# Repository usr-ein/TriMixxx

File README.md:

# TriMixxx

A custom DJ media player — a CDJ-style deck — built from scratch around a Raspberry Pi, designed to run [Mixxx](https://mixxx.org/) DJ software. It reuses an original Pioneer CDJ's buttons and jog wheel behind custom PCBs and a 3D-printed chassis for an authentic DJ feel, and reads Rekordbox-formatted USB sticks — no laptop required.

### The screen

The 1024×600 touchscreen runs a purpose-built Mixxx skin (`mixxx_config/TriMixxx_skin`). There is no mouse and no laptop: every control is either on the deck or under a thumb, so the UI is built around big targets and the browse encoder rather than around pointer precision.

| Playing | Browsing |
|---|---|
|  |  |
| Scrolling waveform with the beat grid, red downbeats anchored on the intro cue, and the whole-track overview underneath. Tempo and pitch sit bottom-right; the header carries artwork, title/artist, the phase meter, elapsed/remaining and the underrun counter. | Rekordbox USBs, the local collection and the Pro DJ Link players lead the menu — the three a deck actually reaches for. The left column sizes itself to its content and follows the selection, and neither pane has a scrollbar: the encoder scrolls them. |

An active loop, set from the deck's hardware loop-in/out buttons, drawn as an amber window over the waveform. Nothing sits below it — the transport, hotcues, loop sizing and tempo range are all physical controls, so the screen gives that space back to the waveform.

## What is this?

TriMixxx replaces the internals of a Pioneer CDJ with modern, open-source-friendly hardware while keeping the physical controls that DJs know and love. Plug in a Rekordbox-formatted USB stick, and you're ready to mix.

Where the CDJ's original main board did everything, TriMixxx today is a **small distributed system**: a Raspberry Pi runs a patched Mixxx behind a custom CDJ-style skin, an ESP32-S3 acts as the controller brain that reads every physical control and speaks MIDI, and a swarm of tiny satellite boards handle the buttons and the LED rings. They all talk over plain TTL UART.

It is a working deck, not a plan: the Pi boots straight into Mixxx, the USB stick automounts, the S3's controls drive it, and Mixxx's feedback drives the LEDs back. Alongside that, `prolinks-compat/` has reverse-engineered Pioneer's ProLink protocol far enough that a real CDJ-2000NXS browses and plays tracks served by this project.

## How we got here (a short history)

This project has been through several complete redesigns. It's worth keeping the lineage straight:

1. **One board to rule them all.** The first idea was a single monolithic PCB carrying *everything*: a Raspberry Pi CM5, a TI PCM5242 I²S DAC with RCA + headphone outputs, USB-C PD power (CH224K + SY8368AQQC buck), dual micro-HDMI, the USB stick ports, and an **ATmega32U4** presenting the CDJ's buttons/jog/fader to the Pi as a USB-MIDI device — all on one board. It was fully routed (`screenshots/CDJ-MainBoard-v1_fully_routed.png`, and the `*_2026-02-17.png` schematic captures) but never became the working unit; cramming compute, audio, power, and a controller onto one board made every revision expensive and every mistake fatal.

2. **Breaking it apart.** The controller was split out onto its own board. `boards/midi-laser-pcb` was the first standalone MIDI-controller PCB — it was fabricated, then abandoned in favour of a cleaner design.

3. **Where it is now.** `boards/midi_s3_mini` is the current controller board (fabricated), hosting a **LOLIN S3 Mini (ESP32-S3)**. The audio DAC and power delivery are no longer TriMixxx's job — a Raspberry Pi handles Mixxx and audio directly, and the S3 is purely the controller brain. The controls are spread across small purpose-built satellite boards, all of them already fabricated.

The old monolithic design is preserved in this README's history and in `screenshots/` as a record of the road not taken.

## Current architecture

```mermaid
flowchart LR
    subgraph PiBox["Raspberry Pi (deck)"]
        Mixxx["Mixxx (patched fork)<br/>+ TriMixxx skin"]
        Tty["ttymidi<br/>trimixxx-bridge.service"]
        Daemon["trimixxx-launchd<br/>(launch manager +<br/>SysEx to the OS)"]
        Usb["dj-usb automount<br/>/media/DJ_USB_*"]
        Doom["Doom (1993)<br/>hold PLAY at boot"]
        Keys["trimixxx-deckkeys<br/>MIDI -> /dev/uinput"]
    end

    S3["midi_s3_mini<br/>LOLIN S3 Mini / ESP32-S3<br/>(controller brain)"]
    RingA["OneButton ring A<br/>CH32V003 nodes<br/>button + 2xWS2812 each"]
    RingB["OneButton ring B<br/>CH32V003 nodes"]
    PlayCue["play_cue_btn<br/>Play / Cue + LEDs"]
    Loop["loop_btn<br/>Loop In/Out/Reloop + LEDs"]
    Jog["Jog wheel<br/>quadrature + touch"]
    CDJ["Real CDJs<br/>(ProLink, Ethernet)"]

    Mixxx <--> Tty
    Mixxx <-->|SysEx| Daemon
    Usb --> Daemon
    Daemon -->|"picks the boot mode"| Mixxx
    Daemon -->|"picks the boot mode"| Doom
    Daemon --> Keys
    Tty -->|"deck buttons"| Daemon
    Tty -->|"deck buttons"| Keys
    Keys -->|"virtual keyboard + mouse"| Doom
    Tty <-->|"UART - raw MIDI - 3.3V"| S3
    S3 <-->|"UART1 - OneButton ring - 5V"| RingA
    S3 <-->|"UART2 - OneButton ring - 5V"| RingB
    S3 --> PlayCue
    S3 --> Loop
    Jog --> S3
    Mixxx -.->|"prolinks-compat (research)"| CDJ
```

- **Raspberry Pi 4B (4 GB)** runs Mixxx — specifically [our own fork](https://github.com/usr-ein/mixxx) (the `mixxx/` submodule), branched off the 2.5.6 tag and carrying deck-specific patches. [`ttymidi`](https://github.com/usr-ein/ttymidi) turns the UART link into an ALSA MIDI device, so Mixxx sees TriMixxx as a standard MIDI controller. That link is 3.3 V on both ends (Pi GPIO ↔ S3), so no level shifting is needed.
- **midi_s3_mini (ESP32-S3)** is the controller brain. It reads every physical control, translates it to MIDI for the Pi, and drives LEDs from the MIDI feedback Mixxx sends back. It runs `firmwares/trimixxx-midi`.
- **Two OneButton rings** hang off the S3, one per UART (A on UART1, B on UART2). Each is a daisy chain of up to 50 CH32V003 nodes, every node carrying one button and two WS2812 LEDs. Nodes enumerate themselves at boot, so a ring self-sizes to however many boards are actually populated (7 and 6 today). See [The OneButton Protocol](#the-onebutton-protocol) below.
- **play_cue_btn** and **loop_btn** are dumb button+LED satellite boards (no MCU) wired to the S3.
- The **jog wheel** (optical quadrature encoder + capacitive touch) wires directly into the S3, decoded by the ESP32's hardware pulse counter (PCNT).

### Signal chain: pressing Play

A worked example of what happens end-to-end, from copper to Mixxx. Every other button on the deck follows the same path.

**Press.** The switch closes and shorts the on-board 100 nF debounce cap to ground, so the GPIO (held high by the S3's internal pull-up) falls low over the RC's time constant — the buttons are active-low. `buttonPollTask` on core 1 samples the pin every `BTN_POLL_MS` = 2 ms and needs `DEBOUNCE` = 3 consecutive stable samples before it accepts the edge, so the RC's slow ramp and any contact bounce are both ignored (~6 ms to accept). Polling is deliberate here rather than an edge interrupt, which slow RC edges tend to upset on the ESP32. On accepting the edge, `poll()` updates the debounced `level` and sets a **sticky press latch**, so the press can't be missed even if the main loop stalls. The main loop (`CTRL_POLL_MS` = 2 ms) calls `playCue.pressed()`, which consumes the latch, and `btnToNote()` hands it to `PiLink`, which writes a Note-On (note `0x3C`, velocity 127) to UART0 at 115200 baud. `ttymidi` on the Pi turns those raw MIDI bytes into an ALSA MIDI event; Mixxx matches `0x3C` in `TriMixxx.midi.xml` and calls `TriMixxx.play`, which toggles the deck's `play` control.

**Held.** Nothing repeats. The sticky latch fires exactly once per press; `btnToNote` keeps a `pending` flag so it knows a Note-Off is still owed. Meanwhile Mixxx sends `play_indicator` back on the same note `0x3C` — `pi.poll()` runs every main-loop pass (no 2 ms gate, for the lowest LED latency) and drives the button's LED from that feedback, so the LED reflects Mixxx's actual state rather than the button's.

**Release.** The switch opens, the pull-up recharges the cap through the RC, and the pin rises. The poll task sees 3 stable high samples, clears `level`, and the next main-loop pass sees `pending && !held` and sends the Note-Off. Mixxx's `TriMixxx.play` ignores value 0, so the release is a no-op there — it just keeps the On/Off pairing well-formed on the wire.

### MIDI map

All MIDI addresses live in one place — `firmwares/trimixxx-midi/lib/PiLink/MidiMap.hpp` — and the Mixxx mapping (`mixxx_config/TriMixxx.midi.xml`) matches them exactly. One deck (v1) → MIDI channel 1.

| Control | MIDI | Mixxx |
|---|---|---|
| Ring A pads (node *i*) | Note `0x00 + i` | Tempo range, keylock, 8/4-beat loops, loop double/halve, back |
| Ring B pads (node *i*) | Note `0x43 + i` | Hotcues 1–4, slip, key-sync indicator |
| Play / Cue | Notes `0x3C` / `0x3D` | `play` (toggle) / `cue_default` |
| Loop In / Out / Reloop | Notes `0x3E` / `0x3F` / `0x40` | `loop_in` / `loop_out` / `reloop_toggle` |
| Track encoder | Note `0x41` (press) + CC `0x10` (relative: 1=up, 127=down) | Browse + load |
| Jog wheel | Note `0x42` (touch/scratch) + CC `0x11` (relative ticks) | Scratch when touched, pitch bend otherwise |
| Tempo fader | CC `0x12` MSB + CC `0x32` LSB (14-bit absolute 0..16383, 8192 = center) | `rate` |

Both pad ranges reserve 50 notes even though fewer nodes are populated today, so growing a ring never renumbers anything.

The tempo fader follows the standard MIDI 14-bit convention — the LSB rides on `MSB + 32` (18 + 32 = 50 = `0x32`) — and Mixxx binds the pair to `[Channel1] rate` with `<fourteen-bit-msb/>` / `<fourteen-bit-lsb/>`. The extra resolution is worth the second CC: a single 7-bit CC would quantise the whole pitch range to 128 steps. The fader is read ratiometrically (wiper minus a live center-tap reference) so the center detent lands on 8192 without calibration.

LED feedback comes back on the same notes. A Note-On velocity only sets *white* brightness, so full RGB travels as SysEx instead — `F0 7D <cmd> <node> <colour nibbles> F7`, with each 8-bit channel split into two data bytes so a 7-bit SysEx payload can still express 0..255 per channel (`0x01` = ring A, `0x03` = ring B). `0x02` reboots the S3, and requires the magic `"RST"` so a stray SysEx can't reset the deck mid-set.

## Boards

All KiCad projects live under `boards/`. Every board below has been fabricated.

| Board | Role | MCU | Status |
|---|---|---|---|
| `midi_s3_mini` | Controller brain: reads all controls, MIDI bridge to the Pi, drives LEDs, jog-wheel input | LOLIN S3 Mini (ESP32-S3) | **Current** |
| `one_button` | Ring node: one button + 2× WS2812, cut-through UART relay. Every node is identical. | CH32V003F4U6 | **Current** |
| `play_cue_btn` | Play + Cue buttons with LEDs (driven by the S3) | none | **Current** |
| `loop_btn` | Loop In/Out/Reloop buttons with LEDs (driven by the S3) | none | **Current** |
| `midi-laser-pcb` | First standalone MIDI-controller board | — | Fabricated, **abandoned** (superseded by `midi_s3_mini`) |

## Firmwares

| Firmware | Runs on | What it is |
|---|---|---|
| `trimixxx-midi` | midi_s3_mini (ESP32-S3) | The master. PlatformIO/Arduino. Reads both OneButton rings + jog wheel + deck controls and bridges them to the Pi as MIDI. Master of both rings. |
| `onebutton` | one_button ring nodes (CH32V003) | Bare-metal [ch32fun](https://github.com/cnlohr/ch32fun). `onebutton_node` (the identical binary every ring node runs) and `onebutton_selftest` (single-board bring-up). |
| `swio-adapter` | A spare Pro Micro | Turns an Arduino into a `minichlink` SWIO programmer for flashing the CH32V003 nodes — no dedicated programmer needed. Git submodule. |
| `ArduinoMIDI` | (historical) | Early ATmega-based MIDI + jog-wheel test sketches from the monolithic-board era. |

Every driver in `trimixxx-midi` is written and live: both rings, jog wheel, tempo fader, track encoder, play/cue board and loop board. A single `DECK_DEBUG` switch at the top of `main.cpp` swaps the MIDI loop for each module's own self-test.

## The OneButton Protocol

The button rings run a purpose-built **cut-through UART ring protocol**. A single fixed-length frame, authored by the S3 master, circulates once around the ring and returns carrying every node's button state; LED colours travel outward on the same frame. Each node forwards bytes as they arrive, editing only the bytes in its own slot, so latency scales as `frame_time + N·byte_time` rather than `N·frame_time`. Node addresses are assigned positionally at boot, so all nodes run an identical binary with no per-unit configuration.

Full wire format, timing, and failure model: **[`firmwares/onebutton/onebutton-protocol.md`](firmwares/onebutton/onebutton-protocol.md)**.

## The Pi side

The deck's software is split into four pieces, each with its own README:

| Piece | What it is |
|---|---|
| `mixxx/` (submodule) | **Our Mixxx fork.** Forked at 2.5.6, carrying deck patches: downbeat highlighting in the waveform (`DownbeatColor` skin node), Rekordbox beat-grid phase preserved via the intro cue, and a `[Rekordbox], refresh` control so a stick mounted mid-set can be picked up from a script. Built for arm64 in Docker and installed over SSH. |
| `mixxx_config/` | Everything under `~/.mixxx`: the controller mapping (`TriMixxx.midi.xml` + `.scripts.js`), the `PiMidiDaemon` mapping, `soundconfig.xml`, and `TriMixxx_skin/` — a single-deck CDJ-style skin for the 1024×600 touchscreen. Its deploy step, `pi-qemu/deploy/005_config.sh`, validates every XML *before* anything leaves the machine, because Qt silently falls back to the default skin on a malformed one. |
| `pi_config/` | The system side: `trimixxx-bridge.service` (ttymidi, ordered before Mixxx so the MIDI port exists when Mixxx enumerates devices), `cpu-governor.service` (the `performance` governor — `ondemand` was the measured cause of xruns while scratching), the session entry points (`bash_profile`, `xinitrc`) that start whichever app the launch manager chose, and `dj-usb/` (udev + systemd read-only automount of DJ sticks). |
| `trimixxx-launcher/` | Two small Go daemons. **`trimixxx-launchd`** does the things Mixxx cannot — its script engine has no file, process or network access, so **MIDI is the only channel out**, and the daemon takes SysEx commands (shutdown, reboot, switch mode) and reports events back (a DJ stick was mounted). It is also the **launch manager**: it reads the deck's own buttons at boot and decides what the deck becomes. **`trimixxx-deckkeys`** replays the deck's MIDI into `/dev/uinput` as a virtual keyboard and mouse. Both ship as fully static musl binaries, so there is nothing to install on the Pi. |
| `doom/` | **The deck plays DOOM (1993).** Hold PLAY while it boots. The jog wheel turns, the tempo fader is the throttle, ring A is the seven weapons. Doom itself is a stock `chocolate-doom` — the controls arrive as a virtual keyboard and mouse, so there is no engine fork here to maintain. |

## ProLink compatibility

`prolinks-compat/` reverse-engineers Pioneer's proprietary **CDJ ProLink** Ethernet protocol so TriMixxx can share libraries with real CDJs on the same network. It is a substantial subproject in its own right — a Python proof-of-concept plus a written specification — and both directions now work against real hardware (two CDJ-2000NXS):

- **Consume:** discover players passively, then pull a deck's `export.pdb` over NFS and list its tracks. The fetched database is byte-identical to the same file read off the physically ejected stick.
- **Serve:** a real CDJ-2000NXS sees us on its LINK screen, browses all eleven categories with drill-downs, sorting, search and harmonic key matching, and **loads and plays tracks** (MP3, AAC, WAV, AIFF) with artwork, hot cues and both waveforms. The last browse session was 568 requests with zero errors.

The protocol as observed is written up in [`prolinks-compat/docs/PROTOCOL.md`](prolinks-compat/docs/PROTOCOL.md), with the evidence behind every claim in `docs/FINDINGS.md` and current state in `STATUS.md`. The end goal is to port the validated approach into Mixxx (C++/Qt) and upstream it.

ProLink can also be tried without the booth: emulated CDJ-2000NXSs, on Pioneer's own firmware, run on a Mac on one network with emulated TriMixxx decks. [`docs/cdj-emulator-quickstart.md`](docs/cdj-emulator-quickstart.md) starts one.

## Chassis

Designed in Fusion 360 to fit the original CDJ form factor — a custom top panel with cutouts for the jog wheel, buttons, and connectors, plus a bottom tray. `ref_sizes/` holds the measured references (CDJ-1000MK3 / 2000NXS2 / 3000 dimensions, jog wheel, screen) the design is built from.

## Repository structure

```
boards/                     KiCad PCB projects
├── midi_s3_mini/               Current controller board (ESP32-S3)
├── one_button/                 OneButton ring node (CH32V003)
├── play_cue_btn/               Play + Cue buttons
├── loop_btn/                   Loop buttons
└── midi-laser-pcb/             Abandoned first controller board

firmwares/                  Embedded firmware
├── trimixxx-midi/              S3 master (PlatformIO / Arduino)
├── onebutton/                  Ring node + selftest (ch32fun)
├── swio-adapter/               CH32V003 SWIO programmer (submodule)
└── ArduinoMIDI/                Historical ATmega sketches

mixxx/                      Our Mixxx fork -- the build the deck runs (submodule)
mixxx_config/               ~/.mixxx: mapping, scripts, skin, sound config
pi_config/                  Pi system config: systemd units, udev, USB automount
trimixxx-launcher/          Go daemons: boot-mode launch manager, SysEx <-> OS,
                            and the MIDI -> virtual keyboard/mouse bridge
doom/                       DOOM (1993) on the deck: WAD, engine config, wrapper

prolinks-compat/            Pioneer ProLink protocol research + Python PoC
ch32fun/                    ch32fun toolkit (submodule)
handmade_pcb/               Hand-etched PCB experiments
datasheet/                  Datasheets for the parts used
ref_sizes/                  Measured CDJ dimensions the chassis is built from
screenshots/                Renders + schematics (incl. the monolithic-board history)
```

## Tools used

- **KiCad** — schematic capture and PCB layout
- **PlatformIO** + **Arduino** — ESP32-S3 firmware
- **ch32fun** — bare-metal CH32V003 firmware and `minichlink` flashing
- **Fusion 360** — mechanical design
- **JLCPCB** — PCB fabrication and assembly
- **Go**, **Python** (`uv`) — Pi daemon and ProLink proof-of-concept

## Trademarks and affiliation

TriMixxx is an independent project with **no affiliation with, sponsorship by, or endorsement from AlphaTheta Corporation** (formerly Pioneer DJ) or the Mixxx project.

**CDJ**, **rekordbox**, **Pro DJ Link**, **DJM**, **NXS/nexus** and **Pioneer DJ** are trademarks of AlphaTheta Corporation. They appear here only to refer to that company's own products — which hardware this project interoperates with, which protocol it speaks, and which units the chassis was measured against. **Mixxx** is the name of the independent open-source project at [mixxx.org](https://mixxx.org/); "TriMixxx" is this project's own name and is not a Mixxx project product.

The ProLink work in `prolinks-compat/` is reverse engineering for **interoperability**, from observation of network traffic between devices the author owns. Protocol facts are not copyrightable, and no code from any reference implementation is copied — see `prolinks-compat/research/10` for the working discipline.

## License

Copyright (C) 2026 Samuel Prevost and contributors.

TriMixxx is free software: you can redistribute it and/or modify it under the terms of the **GNU General Public License version 3** or (at your option) any later version. The full text is in [`LICENSE`](LICENSE). This covers everything in the repository — firmware, host software, hardware sources and documentation alike — except:

- **`prolinks-compat/`**, which is **GPLv2-or-later** on purpose, so it stays compatible with Mixxx and can be upstreamed. GPLv2-or-later code may be used under GPLv3, so this is compatible with the rest of the project; see `prolinks-compat/LICENSE`.
- **Submodules** (`mixxx/`, `ch32fun/`, `firmwares/swio-adapter/`, `mixxx_config/ttymidi/`, the Keebio libraries), which keep their own upstream licenses.

---

## Appendix: the monolithic board (historical)

The original single-board design is no longer built, but its details are recorded here for posterity. It centred on a **Raspberry Pi CM5** (dual DF40 100-pin connectors), a **TI PCM5242** I²S DAC feeding RCA + 6.35 mm + 3.5 mm outputs, an **ATmega32U4** USB-MIDI controller reading all the CDJ controls, USB-C PD power (**CH224K** negotiating 20 V @ 3 A, **SY8368AQQC** buck to 5 V, **AP2112K** LDOs), dual micro-HDMI, gigabit Ethernet, and the USB stick ports (**HD3SS3220**/**HD3SS3212** muxing, **USBLC6-2SC6** ESD protection) — roughly 160 components on one PCB.

### Schematics

| Sheet | File |
|---|---|
| Audio outputs (DAC, RCA, headphones) | `screenshots/audio_2026-02-17.png` |
| MIDI / ATmega controller | `screenshots/midi_arduino_2026-02-17.png` |
| Power delivery (USB-C PD, buck, LDOs) | `screenshots/power_delivery_2026-02-17.png` |
| USB ports (mux, ESD) | `screenshots/usb_2026-02-17.png` |
| Fully routed PCB | `screenshots/CDJ-MainBoard-v1_fully_routed.png` |

### SPICE simulations

- DAC output (PCM5242): `screenshots/dac_spice.png`
- Buck converter (SY8368AQQC): `screenshots/buck_converter_spice.png`

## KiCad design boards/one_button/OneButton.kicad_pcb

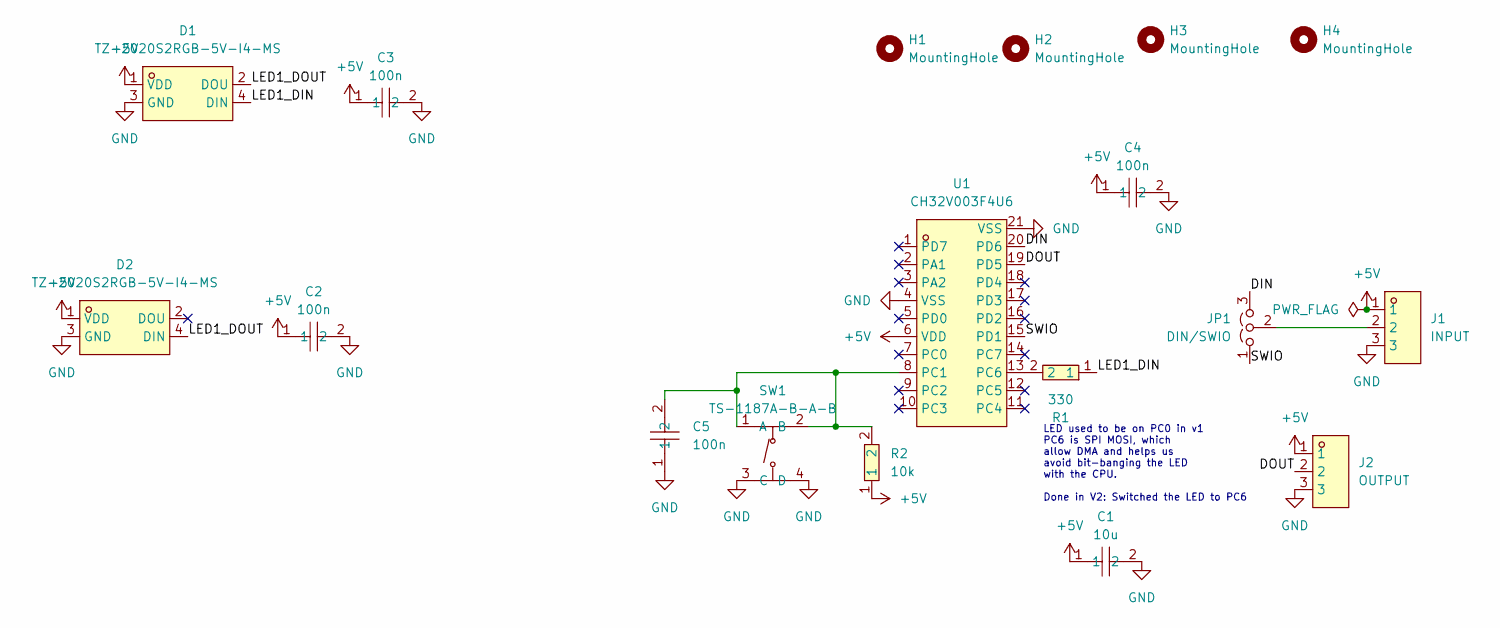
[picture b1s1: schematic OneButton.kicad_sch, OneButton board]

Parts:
C1: 10u; C0603; MPN CL10A106MA8NRNC; LCSC Part C96446
C2, C3, C4, C5: 100n; C0603; MPN CC0603KRX7R9BB104; LCSC Part C14663
D1, D2: TZ-2020S2RGB-5V-I4-MS; LED-SMD_4P-L2.0-W2.0_FZ_2020; MPN TZ-2020S2RGB-5V-I4-MS; LCSC Part C26159668
H1, H2, H3, H4: MountingHole; MountingHole_2.7mm_M2.5_ISO7380
J1: INPUT; CONN-TH_3P-P2.00_S3B-PH-K-S-LF-SN; MPN B3B-PH-K-S(LF)(SN); LCSC Part C131339
J2: OUTPUT; CONN-TH_3P-P2.00_S3B-PH-K-S-LF-SN; MPN B3B-PH-K-S(LF)(SN); LCSC Part C131339
JP1: DIN/SWIO; PinHeader_1x03_P2.54mm_Vertical
R1: 330; R0603; MPN 0603WAF3300T5E; LCSC Part C23138
R2: 10k; R0402; MPN 0402WGF1002TCE; LCSC Part C25744
SW1: TS-1187A-B-A-B; SW-SMD_4P-L5.1-W5.1-P3.70-LS6.5-TL_H1.5; MPN TS-1187A-B-A-B; LCSC Part C318884
U1: CH32V003F4U6; QFN-20_L3.0-W3.0-P0.40-TL-EP1.7; MPN CH32V003F4U6; LCSC Part C5299908

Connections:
+5V: C1.1, C2.1, C3.1, C4.1, D1.1 (VDD), D2.1 (VDD), J1.1, J2.1, R2.1, U1.6 (VDD)
/DIN: JP1.3 (B), U1.20 (PD6)
/DOUT: J2.2, U1.19 (PD5)
/LED1_DIN: D1.4 (DIN), R1.1
/LED1_DOUT: D1.2 (DOU), D2.4 (DIN)
/SWIO: JP1.1 (A), U1.15 (PD1)
GND: C1.2, C2.2, C3.2, C4.2, C5.1, D1.3 (GND), D2.3 (GND), J1.3, J2.3, SW1.3 (C), SW1.4 (D), U1.4 (VSS), U1.21 (VSS)
unnamed: J1.2, JP1.2 (C)
unnamed: C5.2, R2.2, SW1.1 (A), SW1.2 (B), U1.8 (PC1)
unnamed: R1.2, U1.13 (PC6)

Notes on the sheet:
LED used to be on PC0 in v1 PC6 is SPI MOSI, which allow DMA and helps us avoid bit-banging the LED with the CPU. Done in V2: Switched the LED to PC6

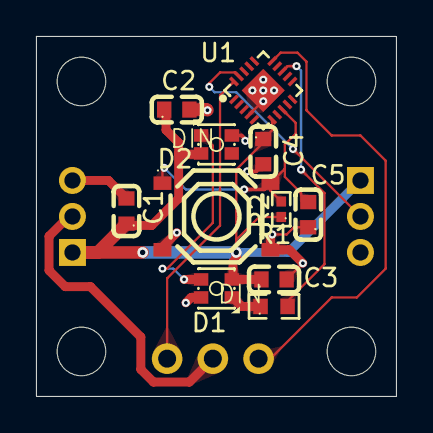
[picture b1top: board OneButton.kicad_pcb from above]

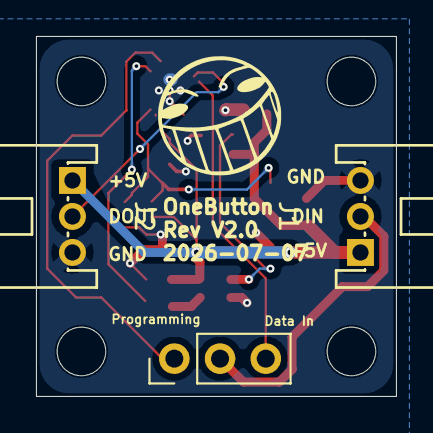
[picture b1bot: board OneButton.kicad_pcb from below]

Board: 2 copper layers, 20.0 x 20.0 mm, 18 parts (3 on the bottom side), 10 nets.

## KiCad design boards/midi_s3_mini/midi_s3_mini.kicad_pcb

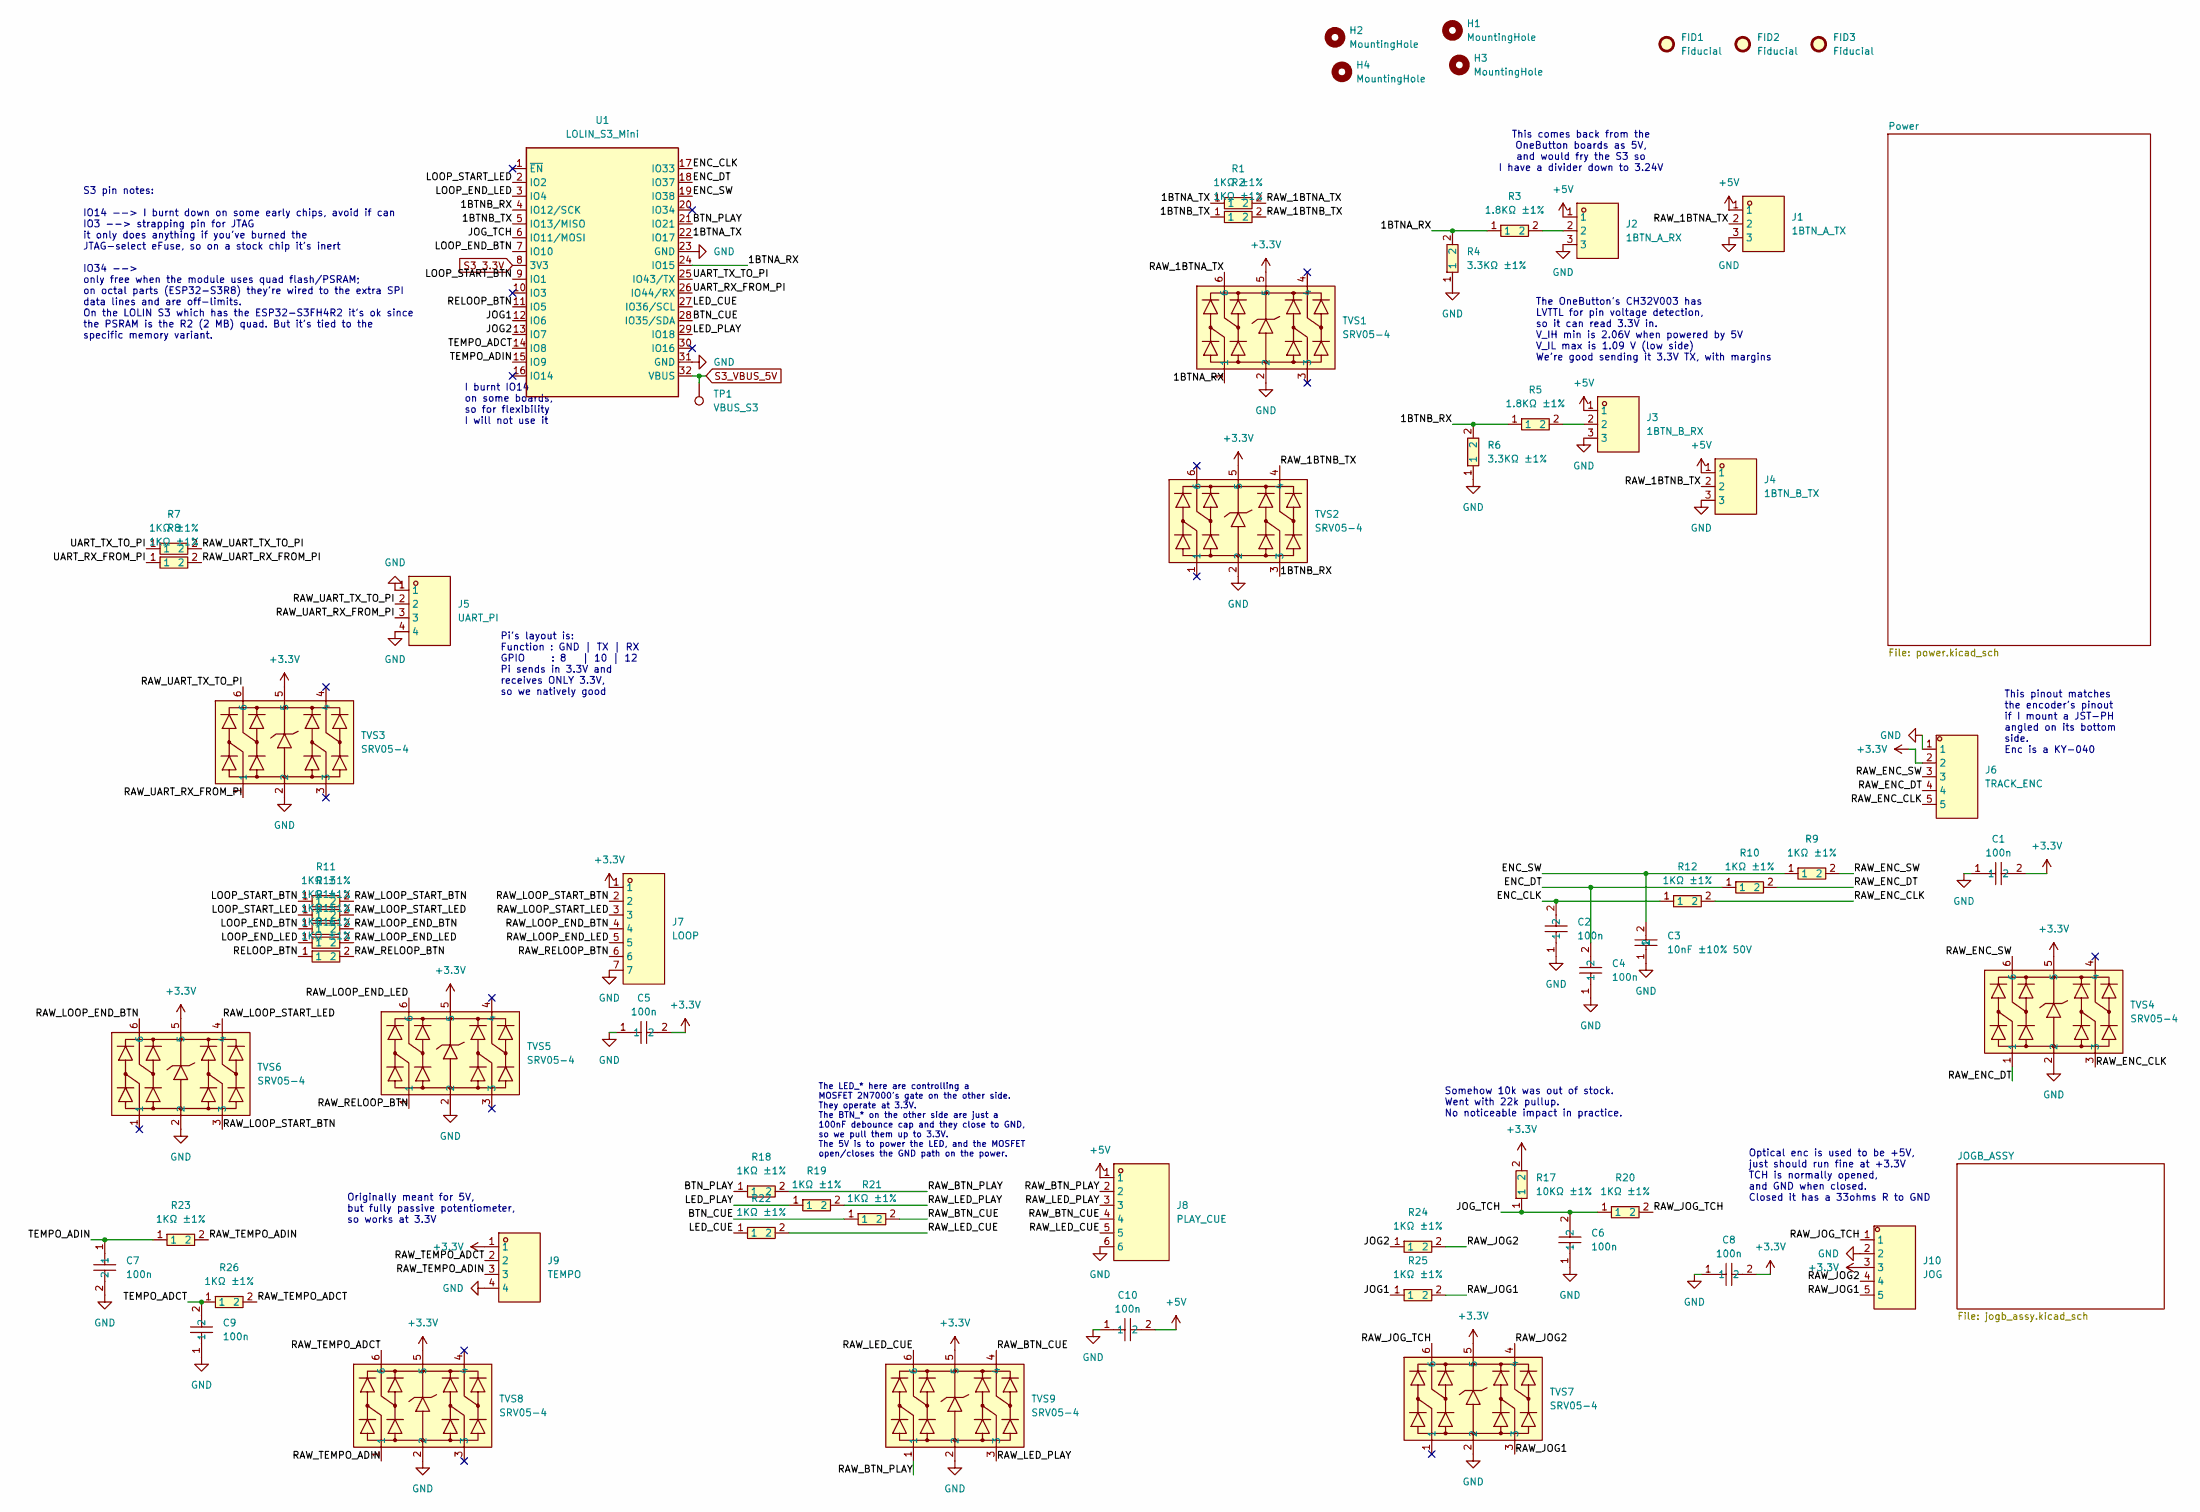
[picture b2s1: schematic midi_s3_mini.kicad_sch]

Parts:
C1, C2, C4, C5, C6, C7, C8, C9, C10: 100n; C0402; MPN CL05B104KB54PNC; LCSC Part C307331
C3: 10nF ±10% 50V; C0402; MPN CL05B103KB5NNNC; LCSC Part C15195
FID1, FID2, FID3: Fiducial; Fiducial_1mm_Mask2mm
H1, H2, H3, H4: MountingHole; MountingHole_4.3mm_M4_ISO7380
J1: 1BTN_A_TX; CONN-TH_3P-P2.00_S3B-PH-K-S-LF-SN; MPN S3B-PH-K-S(LF)(SN); LCSC Part C157929
J2: 1BTN_A_RX; CONN-TH_3P-P2.00_S3B-PH-K-S-LF-SN; MPN S3B-PH-K-S(LF)(SN); LCSC Part C157929
J3: 1BTN_B_RX; CONN-TH_3P-P2.00_S3B-PH-K-S-LF-SN; MPN S3B-PH-K-S(LF)(SN); LCSC Part C157929
J4: 1BTN_B_TX; CONN-TH_3P-P2.00_S3B-PH-K-S-LF-SN; MPN S3B-PH-K-S(LF)(SN); LCSC Part C157929
J5: UART_PI; CONN-TH_4P-P2.00_S4B-PH-K-S-LF-SN; MPN S4B-PH-K-S(LF)(SN); LCSC Part C157926
J6: TRACK_ENC; CONN-TH_S5B-PH-K-S-LF-SN; MPN S5B-PH-K-S(LF)(SN); LCSC Part C157923
J7: LOOP; CONN-TH_7P-P2.00_S7B-PH-K-S-LF-SN; MPN S7B-PH-K-S(LF)(SN); LCSC Part C157917
J8: PLAY_CUE; CONN-TH_6P-P2.00_S6B-PH-K-S-LF-SN; MPN S6B-PH-K-S(LF)(SN); LCSC Part C157920
J9: TEMPO; CONN-TH_4P-P2.00_S4B-PH-K-S-LF-SN; MPN S4B-PH-K-S(LF)(SN); LCSC Part C157926
J10: JOG; CONN-TH_S5B-PH-K-S-LF-SN; MPN S5B-PH-K-S(LF)(SN); LCSC Part C157923
R1, R2, R7, R8, R9, R10, R11, R12, R13, R14, R15, R16, R18, R19, R20, R21, R22, R23, R24, R25, R26: 1KΩ ±1%; R0402; MPN 0402WGF1001TCE; LCSC Part C11702
R3, R5: 1.8KΩ ±1%; R0603; MPN 0603WAF1801T5E; LCSC Part C4177
R4, R6: 3.3KΩ ±1%; R0402; MPN 0402WGF3301TCE; LCSC Part C25890
R17: 10KΩ ±1%; R0402; MPN 0402WGF1002TCE; LCSC Part C25744
TP1: VBUS_S3; TestPoint_Pad_D2.5mm
TVS1, TVS2, TVS3, TVS4, TVS5, TVS6, TVS7, TVS8, TVS9: SRV05-4; SOT-23-6_L2.9-W1.6-P0.95-LS2.8-BL; MPN SRV05-4; LCSC Part C558418
U1: LOLIN_S3_Mini

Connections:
+3.3V: C1.2, C5.2, C8.2, J6.2, J7.1, J9.1, J10.3, R17.2, TVS1.5, TVS2.5, TVS3.5, TVS4.5, TVS5.5, TVS6.5, TVS7.5, TVS8.5, TVS9.5; also elsewhere on the board
+5V: C10.2, J1.1, J2.1, J3.1, J4.1, J8.1; also elsewhere on the board
/1BTNA_RX: R3.1, R4.2, TVS1.1, U1.24 (IO15)
/1BTNA_TX: R1.1, U1.22 (IO17)
/1BTNB_RX: R5.1, R6.2, TVS2.3, U1.4 (IO12/SCK)
/1BTNB_TX: R2.1, U1.5 (IO13/MISO)
/BTN_CUE: R21.1, U1.28 (IO35/SDA)
/BTN_PLAY: R18.1, U1.21 (IO21)
/ENC_CLK: C2.2, R12.1, U1.17 (IO33)
/ENC_DT: C4.2, R10.1, U1.18 (IO37)
/ENC_SW: C3.2, R9.1, U1.19 (IO38)
/JOG1: R25.1, U1.12 (IO6)
/JOG2: R24.1, U1.13 (IO7)
/JOG_TCH: C6.2, R17.1, R20.1, U1.6 (IO11/MOSI)
/LED_CUE: R22.1, U1.27 (IO36/SCL)
/LED_PLAY: R19.1, U1.29 (IO18)
/LOOP_END_BTN: R14.1, U1.7 (IO10)
/LOOP_END_LED: R15.1, U1.3 (IO4)
/LOOP_START_BTN: R11.1, U1.9 (IO1)
/LOOP_START_LED: R13.1, U1.2 (IO2)
/RAW_1BTNA_TX: J1.2, R1.2, TVS1.6
/RAW_1BTNB_TX: J4.2, R2.2, TVS2.4
/RAW_BTN_CUE: J8.4, R21.2, TVS9.4
/RAW_BTN_PLAY: J8.2, R18.2, TVS9.1
/RAW_ENC_CLK: J6.5, R12.2, TVS4.3
/RAW_ENC_DT: J6.4, R10.2, TVS4.1
/RAW_ENC_SW: J6.3, R9.2, TVS4.6
/RAW_JOG1: J10.5, R25.2, TVS7.3
/RAW_JOG2: J10.4, R24.2, TVS7.4
/RAW_JOG_TCH: J10.1, R20.2, TVS7.6
/RAW_LED_CUE: J8.5, R22.2, TVS9.6
/RAW_LED_PLAY: J8.3, R19.2, TVS9.3
/RAW_LOOP_END_BTN: J7.4, R14.2, TVS6.6
/RAW_LOOP_END_LED: J7.5, R15.2, TVS5.6
/RAW_LOOP_START_BTN: J7.2, R11.2, TVS6.3
/RAW_LOOP_START_LED: J7.3, R13.2, TVS6.4
/RAW_RELOOP_BTN: J7.6, R16.2, TVS5.1
/RAW_TEMPO_ADCT: J9.2, R26.2, TVS8.6
/RAW_TEMPO_ADIN: J9.3, R23.2, TVS8.1
/RAW_UART_RX_FROM_PI: J5.3, R8.2, TVS3.1
/RAW_UART_TX_TO_PI: J5.2, R7.2, TVS3.6
/RELOOP_BTN: R16.1, U1.11 (IO5)
/TEMPO_ADCT: C9.2, R26.1, U1.14 (IO8)
/TEMPO_ADIN: C7.1, R23.1, U1.15 (IO9)
/UART_RX_FROM_PI: R8.1, U1.26 (IO44/RX)
/UART_TX_TO_PI: R7.1, U1.25 (IO43/TX)
GND: C1.1, C2.1, C3.1, C4.1, C5.1, C6.1, C7.2, C8.1, C9.1, C10.1, J1.3, J2.3, J3.3, J4.3, J5.1, J5.4, J6.1, J7.7, J8.6, J9.4, J10.2, R4.1, R6.1, TVS1.2, TVS2.2, TVS3.2, TVS4.2, TVS5.2, TVS6.2, TVS7.2, TVS8.2, TVS9.2, U1.23 (GND), U1.31 (GND); also elsewhere on the board
unnamed: J2.2, R3.2
unnamed: J3.2, R5.2
S3_3.3V: U1.8 (3V3); also elsewhere on the board
S3_VBUS_5V: TP1.1 (1_1), U1.32 (VBUS); also elsewhere on the board

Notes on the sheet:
I burnt IO14 on some boards, so for flexibility I will not use it
The LED_* here are controlling a MOSFET 2N7000's gate on the other side. They operate at 3.3V. The BTN_* on the other side are just a 100nF debounce cap and they close to GND, so we pull them up to 3.3V. The 5V is to power the LED, and the MOSFET open/closes the GND path on the power.
S3 pin notes: IO14 --> I burnt down on some early chips, avoid if can IO3 --> strapping pin for JTAG it only does anything if you've burned the JTAG-select eFuse, so on a stock chip it's inert IO34 --> only free when the module uses quad flash/PSRAM; on octal parts (ESP32-S3R8) they're wired to the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
Optical enc is used to be +5V, just should run fine at +3.3V TCH is normally opened, and GND when closed. Closed it has a 33ohms R to GND
The OneButton's CH32V003 has LVTTL for pin voltage detection, so it can read 3.3V in. V_IH min is 2.06V when powered by 5V V_IL max is 1.09 V (low side) We're good sending it 3.3V TX, with margins
This comes back from the OneButton boards as 5V, and would fry the S3 so I have a divider down to 3.24V
This pinout matches the encoder's pinout if I mount a JST-PH angled on its bottom side. Enc is a KY-040
Pi's layout is: Function : GND | TX | RX GPIO : 8 | 10 | 12 Pi sends in 3.3V and receives ONLY 3.3V, so we natively good
Originally meant for 5V, but fully passive potentiometer, so works at 3.3V
Somehow 10k was out of stock. Went with 22k pullup. No noticeable impact in practice.

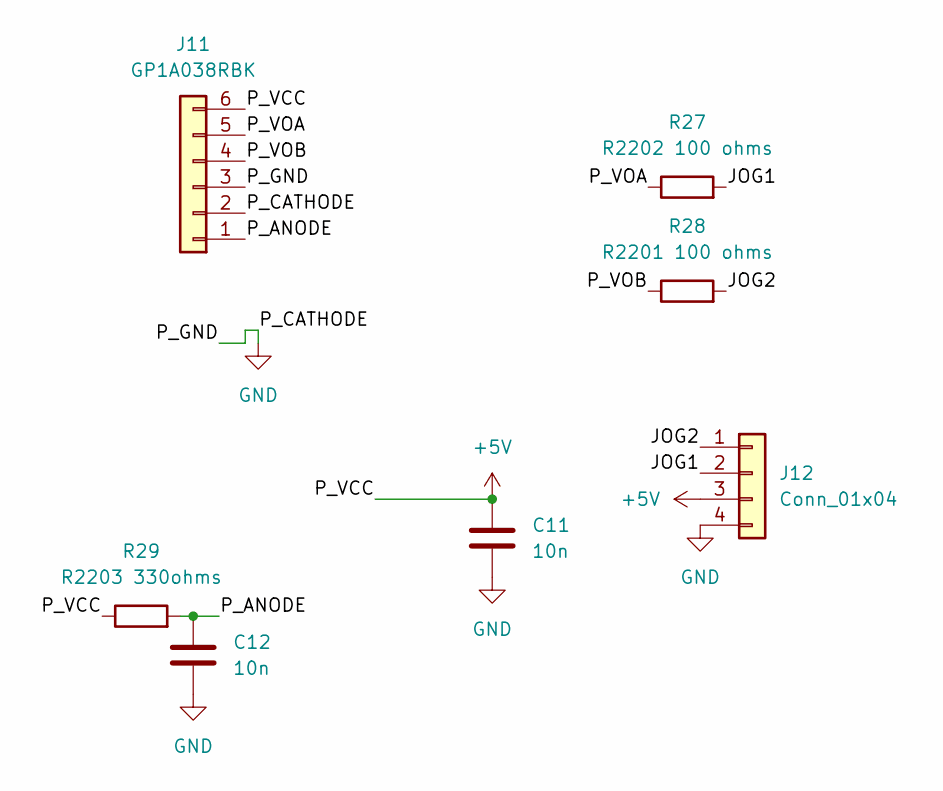
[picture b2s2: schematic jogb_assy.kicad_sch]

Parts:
C11, C12: 10n
J11: GP1A038RBK
J12: Conn_01x04
R27: R2202 100 ohms
R28: R2201 100 ohms
R29: R2203 330ohms

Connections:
unnamed: C11.1, J11.6, J12.3, R29.1
unnamed: C11.2, C12.2, J11.2, J11.3, J12.4
unnamed: C12.1, J11.1, R29.2
unnamed: J11.4, R28.1
unnamed: J11.5, R27.1
unnamed: J12.1, R28.2
unnamed: J12.2, R27.2

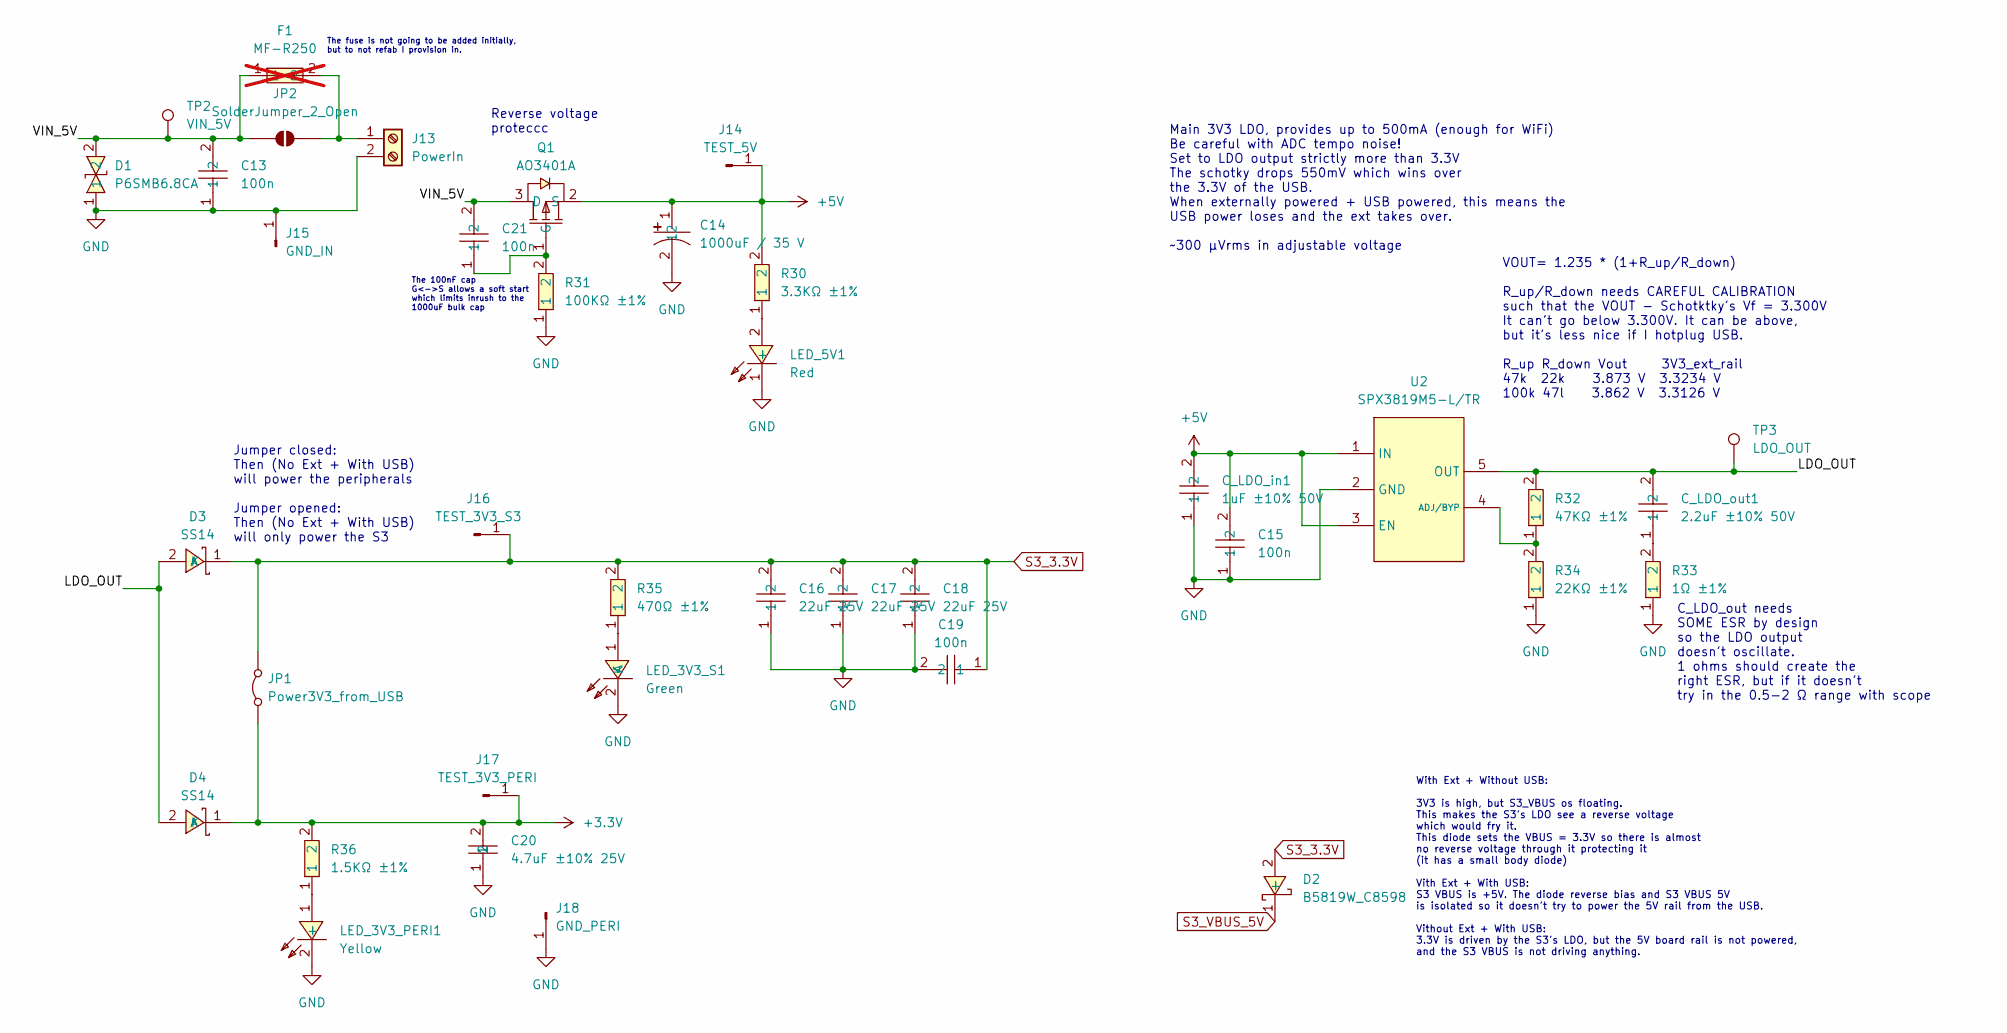
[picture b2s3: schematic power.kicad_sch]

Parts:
C13, C15, C19, C21: 100n; C0402; MPN CL05B104KB54PNC; LCSC Part C307331
C14: 1000uF / 35 V; CAP-TH_BD10.0-P5.00-D1.0-FD; MPN ERR1VM102G20OT; LCSC Part C398835
C16, C17, C18: 22uF 25V; C0805; MPN CL21A226MAQNNNE; LCSC Part C45783
C20: 4.7uF ±10% 25V; C0805; MPN CL21A475KAQNNNE; LCSC Part C1779
C_LDO_in1: 1uF ±10% 50V; C0603; MPN CL10A105KB8NNNC; LCSC Part C15849
C_LDO_out1: 2.2uF ±10% 50V; C0805; MPN CL21A225KBQNNNE; LCSC Part C377773
D1: P6SMB6.8CA; SMB_L4.6-W3.6-LS5.3-BI; MPN P6SMB6.8CA/TR13; LCSC Part C78395
D2: B5819W_C8598; SOD-123_L2.7-W1.6-LS3.7-RD-1; MPN B5819W SL; LCSC Part C8598
D3, D4: SS14; SMA_L4.2-W2.6-LS5.0-RD_1; MPN SS14; LCSC Part C2480
F1: MF-R250; FUSE-TH_L12.8-W3.0-P5.80-D1.2-S2.20; MPN MF-R250; LCSC Part C208486; not fitted
J13: PowerIn; Altech_AK300_1x02_P5.00mm_45-Degree
J14: TEST_5V; PinHeader_1x01_P2.54mm_Vertical
J15: GND_IN; PinHeader_1x01_P2.54mm_Vertical
J16: TEST_3V3_S3; PinHeader_1x01_P2.54mm_Vertical
J17: TEST_3V3_PERI; PinHeader_1x01_P2.54mm_Vertical
J18: GND_PERI; PinHeader_1x01_P2.54mm_Vertical
JP1: Power3V3_from_USB; PinHeader_1x02_P2.54mm_Vertical
JP2: SolderJumper_2_Open; SolderJumper-2_P1.3mm_Open_TrianglePad1.0x1.5mm
LED_3V3_PERI1: Yellow; LED0805-R-RD; MPN KT-0805黄灯; LCSC Part C2296
LED_3V3_S1: Green; LED0805-R-RD; MPN KT-0805G; LCSC Part C2297
LED_5V1: Red; LED0805-RD; MPN NCD0805R1; LCSC Part C84256
Q1: AO3401A; SOT-23_L2.9-W1.3-P1.90-LS2.4-BR; MPN AO3401A; LCSC Part C15127
R30: 3.3KΩ ±1%; R0402; MPN 0402WGF3301TCE; LCSC Part C25890
R31: 100KΩ ±1%; R0603; MPN 0603WAF1003T5E; LCSC Part C25803
R32: 47KΩ ±1%; R0402; MPN 0402WGF4702TCE; LCSC Part C25792
R33: 1Ω ±1%; R0402; MPN 0402WGF100KTCE; LCSC Part C25086
R34: 22KΩ ±1%; R0402; MPN 0402WGF2202TCE; LCSC Part C25768
R35: 470Ω ±1%; R0402; MPN 0402WGF4700TCE; LCSC Part C25117
R36: 1.5KΩ ±1%; R0402; MPN 0402WGF1501TCE; LCSC Part C25867
TP2: VIN_5V; TestPoint_Pad_D2.5mm
TP3: LDO_OUT; TestPoint_Pad_D2.5mm
U2: SPX3819M5-L/TR; SOT-23-5_L3.0-W1.7-P0.95-LS2.8-TL; MPN SPX3819M5-L/TR; LCSC Part C9056

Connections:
+3.3V: C20.2, D4.1 (K), J17.1 (Pin_1_1), JP1.1 (A), R36.2; also elsewhere on the board
+5V: C14.1, C15.2, C_LDO_in1.2, J14.1 (Pin_1_1), Q1.2 (S), R30.2, U2.1 (IN), U2.3 (EN); also elsewhere on the board
/Power/LDO_OUT: C_LDO_out1.2, D3.2 (A), D4.2 (A), R32.2, TP3.1 (1_1), U2.5 (OUT)
/Power/VIN_5V: C13.2, C21.2, D1.2, F1.1, JP2.1 (A), Q1.3 (D), TP2.1 (1_1)
GND: C13.1, C14.2, C15.1, C16.1, C17.1, C18.1, C19.2, C20.1, C_LDO_in1.1, D1.1, J13.2, J15.1 (Pin_1_1), J18.1 (Pin_1_1), LED_3V3_PERI1.2 (-), LED_3V3_S1.2 (K), LED_5V1.1 (-), R31.1, R33.1, R34.1, U2.2 (GND); also elsewhere on the board
unnamed: C_LDO_out1.1, R33.2
unnamed: F1.2, J13.1, JP2.2 (B)
unnamed: LED_3V3_PERI1.1 (+), R36.1
unnamed: LED_3V3_S1.1 (A), R35.1
unnamed: LED_5V1.2 (+), R30.1
unnamed: C21.1, Q1.1 (G), R31.2
unnamed: R32.1, R34.2, U2.4 (ADJ/BYP)
S3_3.3V: C16.2, C17.2, C18.2, C19.1, D2.2 (+), D3.1 (K), J16.1 (Pin_1_1), JP1.2 (B), R35.2; also elsewhere on the board
S3_VBUS_5V: D2.1 (-); also elsewhere on the board

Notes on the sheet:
The 100nF cap G<->S allows a soft start which limits inrush to the 1000uF bulk cap
With Ext + Without USB: 3V3 is high, but S3_VBUS os floating. This makes the S3's LDO see a reverse voltage which would fry it. This diode sets the VBUS = 3.3V so there is almost no reverse voltage through it protecting it (it has a small body diode) Vith Ext + With USB: S3 VBUS is +5V. The diode r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
Jumper closed: Then (No Ext + With USB) will power the peripherals Jumper opened: Then (No Ext + With USB) will only power the S3
VOUT= 1.235 * (1+R_up/R_down) R_up/R_down needs CAREFUL CALIBRATION such that the VOUT - Schotktky's Vf = 3.300V It can't go below 3.300V. It can be above, but it's less nice if I hotplug USB. R_up R_down Vout 3V3_ext_rail 47k 22k 3.873 V 3.3234 V 100k 47l 3.862 V 3.3126 V
C_LDO_out needs SOME ESR by design so the LDO output doesn't oscillate. 1 ohms should create the right ESR, but if it doesn't try in the 0.5-2 Ω range with scope
Reverse voltage proteccc
Main 3V3 LDO, provides up to 500mA (enough for WiFi) Be careful with ADC tempo noise! Set to LDO output strictly more than 3.3V The schotky drops 550mV which wins over the 3.3V of the USB. When externally powered + USB powered, this means the USB power loses and the ext takes over. ~300 µVrms in ad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
The fuse is not going to be added initially, but to not refab I provision in.

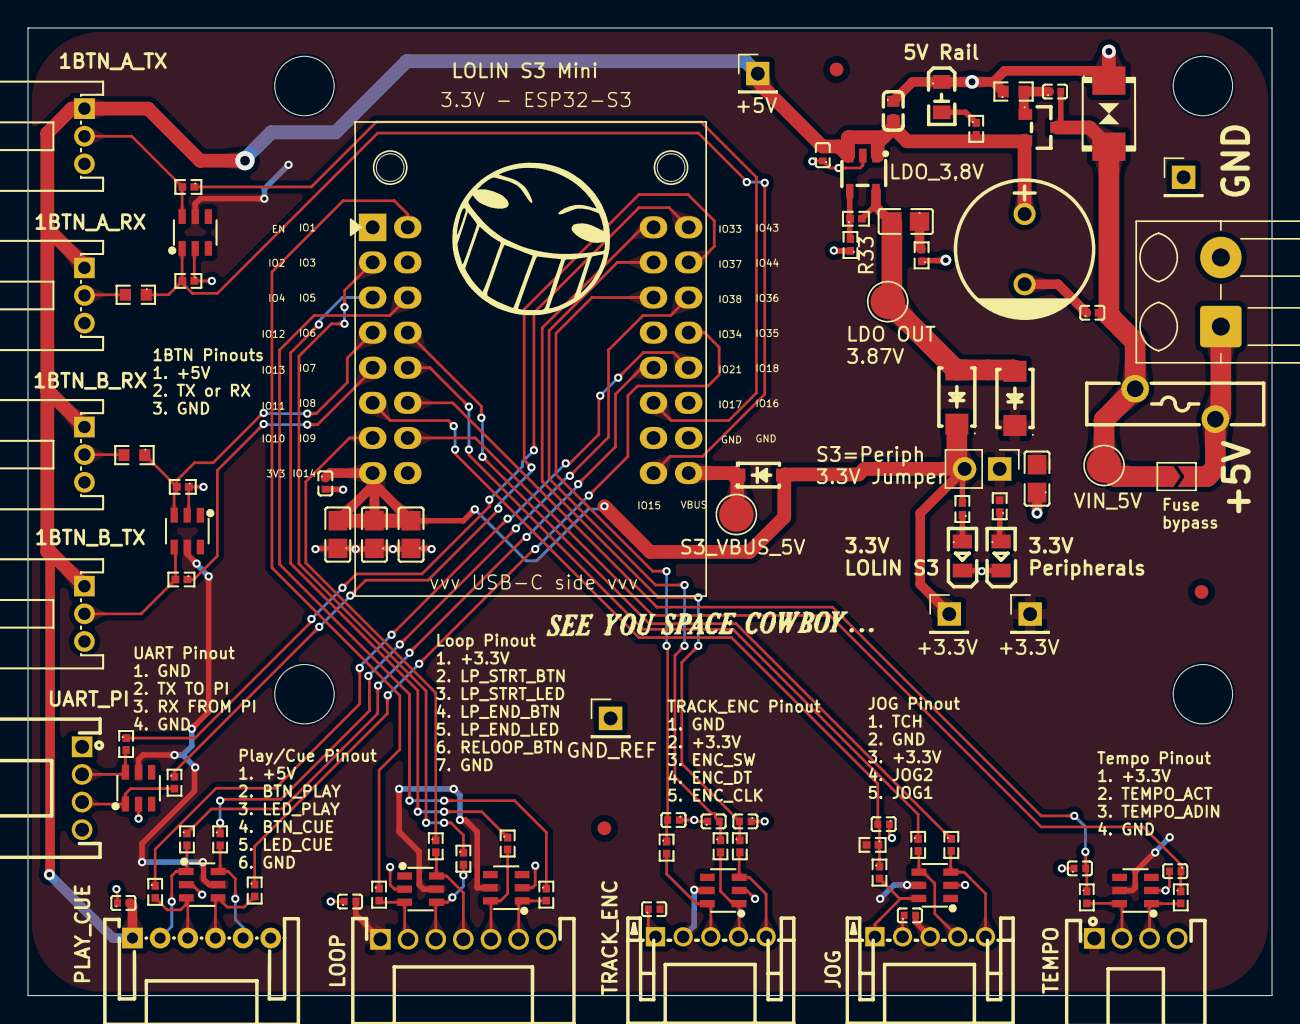
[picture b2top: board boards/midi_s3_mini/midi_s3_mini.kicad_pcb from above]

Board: 2 copper layers, 90.0 x 70.0 mm, 102 parts (0 on the bottom side), 60 nets.

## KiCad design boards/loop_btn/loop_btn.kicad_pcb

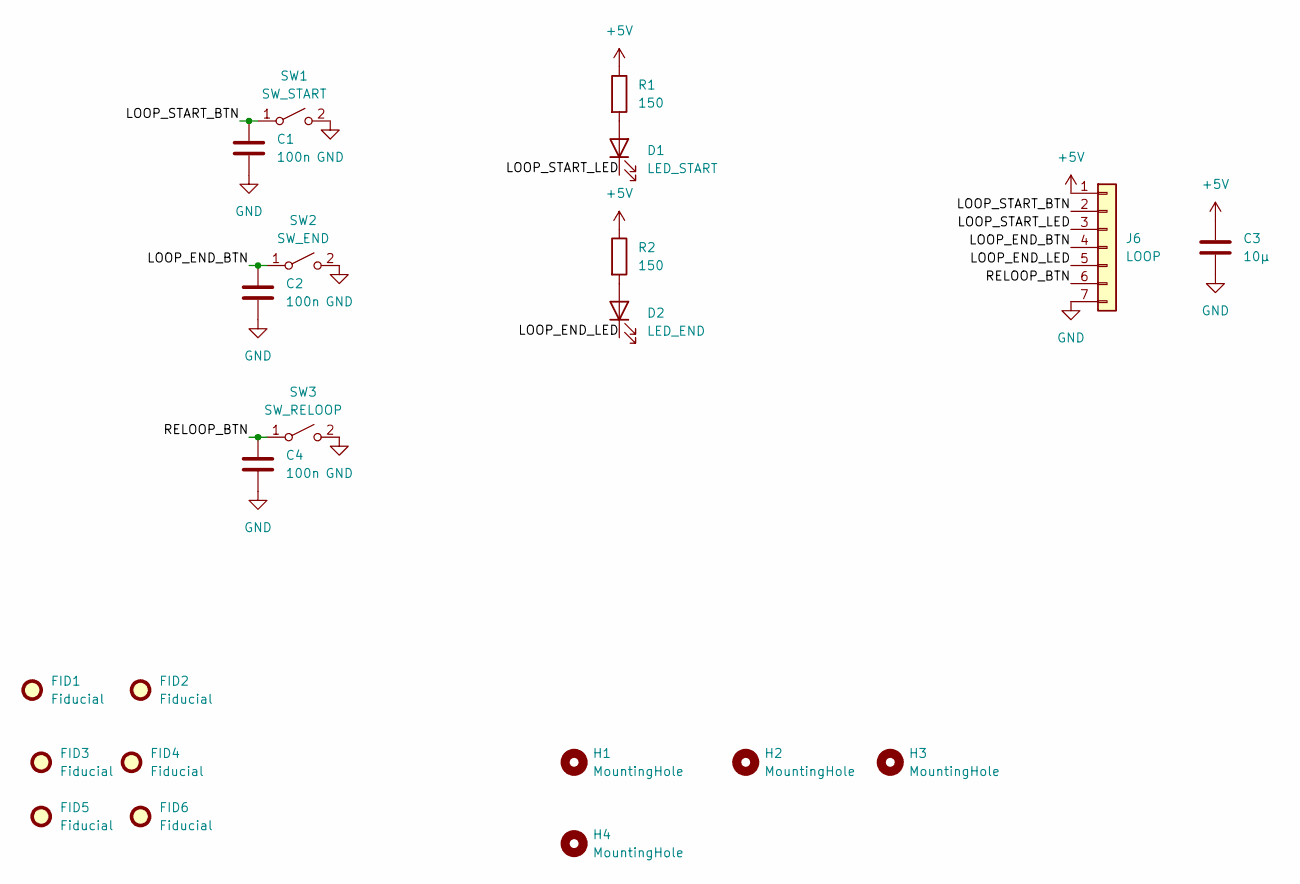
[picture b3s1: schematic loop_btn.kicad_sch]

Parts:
C1, C2, C4: 100n; C_Disc_D5.0mm_W2.5mm_P5.00mm
C3: 10µ; C_Disc_D5.0mm_W2.5mm_P5.00mm
D1: LED_START; LED_D5.0mm
D2: LED_END; LED_D5.0mm
FID1, FID2, FID3, FID4, FID5, FID6: Fiducial; Fiducial_Cross_1.5mm_Mask2mm
H1, H2, H3, H4: MountingHole; MountingHole_3.2mm_M3
J6: LOOP; JST_XH_B7B-XH-AM_1x07_P2.50mm_Vertical
R1, R2: 150; R_Axial_DIN0207_L6.3mm_D2.5mm_P7.62mm_Horizontal
SW1: SW_START; SW_PUSH_6mm_H4.3mm
SW2: SW_END; SW_PUSH_6mm_H4.3mm
SW3: SW_RELOOP; SW_PUSH_6mm_H4.3mm

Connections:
+5V: C3.1, J6.1, R1.1, R2.1
/LOOP_END_BTN: C2.1, J6.4, SW2.1 (A)
/LOOP_END_LED: D2.1 (K), J6.5
/LOOP_START_BTN: C1.1, J6.2, SW1.1 (A)
/LOOP_START_LED: D1.1 (K), J6.3
/RELOOP_BTN: C4.1, J6.6, SW3.1 (A)
GND: C1.2, C2.2, C3.2, C4.2, J6.7, SW1.2 (B), SW2.2 (B), SW3.2 (B)
unnamed: D1.2 (A), R1.2
unnamed: D2.2 (A), R2.2
